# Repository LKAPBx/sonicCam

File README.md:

# sonicCam
Sound Camera

Project created in KiCad.

An array of digital MEMS microphones connected to a single clock source. 

It contains the following:

 1. A 2 row, 40-pin 100mil spacing connection header.
 2. A major array that consists of 16 microphones spaced equally across the PCB.
 2. Two minor arrays of 9 microphones that make up the 'lower left' and 'upper right' quadrants of the major array.
 3. A temperature and pressure sensor with clock selection jumper resistors.
 4. An ultra-sonic speaker and amp.
 5. An option header to allow multiple arrays to be ganged together on the same ribbon cable.

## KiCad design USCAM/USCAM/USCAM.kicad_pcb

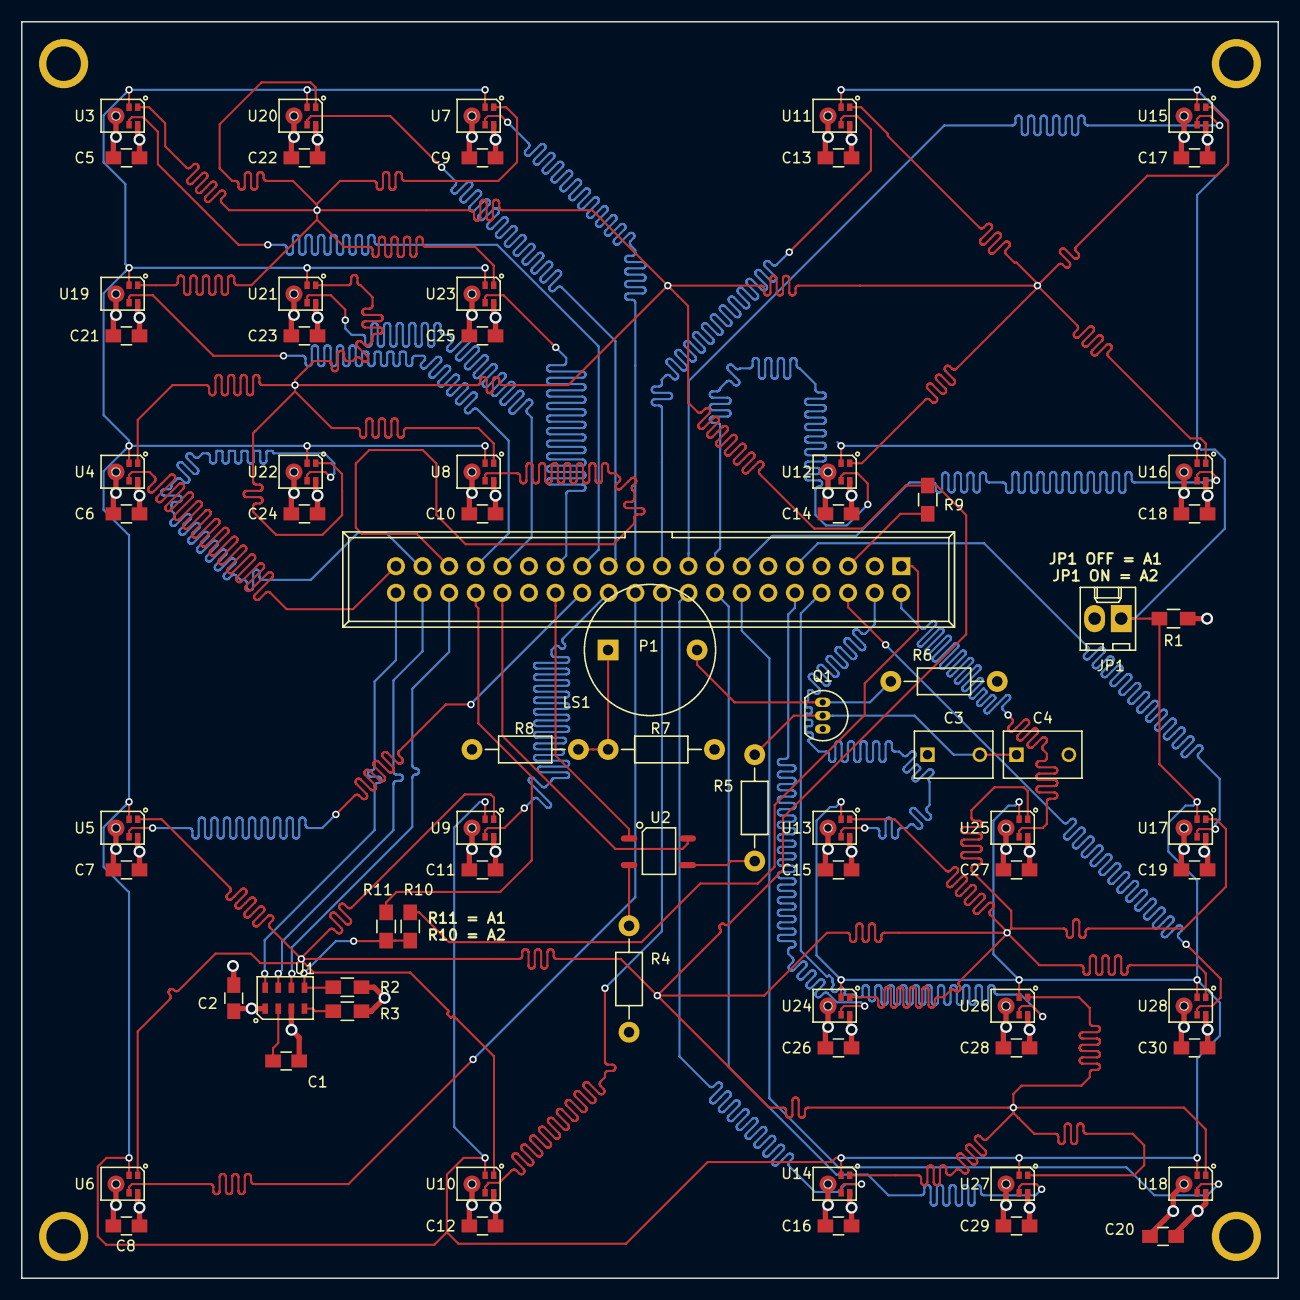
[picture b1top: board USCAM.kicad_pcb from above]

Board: 4 copper layers, 120.0 x 120.0 mm, 77 parts (0 on the bottom side), 47 nets.

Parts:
C1, C2: 1UF; C_0805_HandSoldering
C3, C4: 0.1UF; C_Disc_D7.5_P5
C5, C6, C7, C8, C9, C10, C11, C12, C13, C14, C15, C16, C17, C18, C19, C20, C21, C22, C23, C24, C25, C26, C27, C28, C29, C30: 0.1UF; C_0805_HandSoldering
JP1: CONN_01X02; Molex_KK-6410-02_02x2.54mm_Straight
LS1: UR-1240K-TT-4; UR-1240K-TT-R
MT1, MT2, MT3, MT4: 4-40_HOLE
P1: CONN_02X20; IDC_Header_Straight_40pins
Q1: BC337; TO-92_Inline_Narrow_Oval
R1, R2, R3: 10K; R_0805_HandSoldering
R4: 425; Resistor_Horizontal_RM10mm
R5: 10K; Resistor_Horizontal_RM10mm
R6: 390; Resistor_Horizontal_RM10mm
R7, R8: 220; Resistor_Horizontal_RM10mm
R9, R10, R11: 22; R_0805_HandSoldering
U1: MPL115A1; LGA8
U2: CPC1025N; SOP4_HS
U3, U4, U5, U6, U7, U8, U9, U10, U11, U12, U13, U14, U15, U16, U17, U18, U19, U20, U21, U22, U23, U24, U25, U26, U27, U28: SPH0641LU4H-1

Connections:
+3V3: C2.1, C5.1, C6.1, C7.1, C8.1, C9.1, C10.1, C11.1, C12.1, C13.1, C14.1, C15.1, C16.1, C17.1, C18.1, C19.1, C20.1, C21.1, C22.1, C23.1, C24.1, C25.1, C26.1, C27.1, C28.1, C29.1, C30.1, P1.29, R1.1, R2.1, R3.1, U1.1, U3.5, U4.5, U5.5, U6.5, U7.5, U8.5, U9.5, U10.5, U11.5, U12.5, U13.5, U14.5, U15.5, U16.5, U17.5, U18.5, U19.5, U20.5, U21.5, U22.5, U23.5, U24.5, U25.5, U26.5, U27.5, U28.5
+5V: C3.1, P1.11, R6.2, R7.2
/BAROMETER/TP_DIN: P1.38, U1.7
/BAROMETER/TP_DOUT: P1.36, U1.6
/BAROMETER/TP_SCLK: P1.40, U1.8
/BAROMETER/~TP_CS: R2.2, R10.1, R11.1, U1.5
/MAJOR_ARRAY/MD1: P1.25, U3.4
/MAJOR_ARRAY/MD2: P1.39, U4.4
/MAJOR_ARRAY/MD3: P1.26, U5.4
/MAJOR_ARRAY/MD4: P1.22, U6.4
/MAJOR_ARRAY/MD5: P1.21, U7.4
/MAJOR_ARRAY/MD6: P1.35, U8.4
/MAJOR_ARRAY/MD7: P1.24, U9.4
/MAJOR_ARRAY/MD8: P1.20, U10.4
/MAJOR_ARRAY/MD9: P1.19, U11.4
/MAJOR_ARRAY/MD10: P1.15, U12.4
/MAJOR_ARRAY/MD11: P1.4, U13.4
/MAJOR_ARRAY/MD12: P1.18, U14.4
/MAJOR_ARRAY/MD13: P1.17, U15.4
/MAJOR_ARRAY/MD14: P1.13, U16.4
/MAJOR_ARRAY/MD15: P1.9, U17.4
/MAJOR_ARRAY/MD16: P1.14, U18.4
/MINOR_ARRAY_NW/MD17: P1.33, U19.4
/MINOR_ARRAY_NW/MD18: P1.23, U20.4
/MINOR_ARRAY_NW/MD19: P1.31, U21.4
/MINOR_ARRAY_NW/MD20: P1.37, U22.4
/MINOR_ARRAY_NW/MD21: P1.27, U23.4
/MINOR_ARRAY_SE/MD22: P1.10, U24.4
/MINOR_ARRAY_SE/MD23: P1.2, U25.4
/MINOR_ARRAY_SE/MD24: P1.8, U26.4
/MINOR_ARRAY_SE/MD25: P1.16, U27.4
/MINOR_ARRAY_SE/MD26: P1.6, U28.4
/USONIC_OUT/UOUT_EN: P1.28, U2.1
/USONIC_OUT/UOUT_IN: P1.32, U2.4
GND: C1.2, C2.2, C4.2, C5.2, C6.2, C7.2, C8.2, C9.2, C10.2, C11.2, C12.2, C13.2, C14.2, C15.2, C16.2, C17.2, C18.2, C19.2, C20.2, C21.2, C22.2, C23.2, C24.2, C25.2, C26.2, C27.2, C28.2, C29.2, C30.2, JP1.2, P1.12, P1.30, Q1.3, R4.1, R8.1, U1.3, U3.3, U4.3, U5.3, U6.3, U7.3, U8.3, U9.3, U10.3, U11.3, U12.3, U13.3, U14.3, U15.3, U16.3, U17.3, U18.3, U19.3, U20.3, U21.3, U22.3, U23.3, U24.3, U25.3, U26.3, U27.3, U28.3
MCLK_IN: R9.2, U3.1, U4.1, U5.1, U6.1, U7.1, U8.1, U9.1, U10.1, U11.1, U12.1, U13.1, U14.1, U15.1, U16.1, U17.1, U18.1, U19.1, U20.1, U21.1, U22.1, U23.1, U24.1, U25.1, U26.1, U27.1, U28.1
MDSEL: JP1.1, R1.2, U3.2, U4.2, U5.2, U6.2, U7.2, U8.2, U9.2, U10.2, U11.2, U12.2, U13.2, U14.2, U15.2, U16.2, U17.2, U18.2, U19.2, U20.2, U21.2, U22.2, U23.2, U24.2, U25.2, U26.2, U27.2, U28.2
unnamed: C1.1, U1.2
unnamed: C3.2, C4.1, Q1.2, R5.1
unnamed: LS1.1, R7.1, R8.2
unnamed: LS1.2, Q1.1, R6.1
unnamed: P1.1, R10.2
unnamed: P1.5, R9.1
unnamed: P1.34, R11.2
unnamed: R3.2, U1.4
unnamed: R4.2, U2.2
unnamed: R5.2, U2.3

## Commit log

2016-08-03 Initial
